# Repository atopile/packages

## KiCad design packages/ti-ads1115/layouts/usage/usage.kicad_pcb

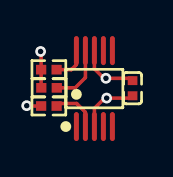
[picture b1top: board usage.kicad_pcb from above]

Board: 2 copper layers, 5 parts (0 on the bottom side), 6 nets.

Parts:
C1: 100nF; C0402
R1, R2, R3: 10kΩ; R0402
U1: MSOP-10_L3.0-W3.0-P0.50-LS5.0-BL

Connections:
ALERT_RDY: R1.1, U1.2
SCL: R2.1, U1.10
SDA: R3.1, U1.9
hv: C1.1, U1.8
i2c-hv: R2.2, R3.2
lv: C1.2, U1.1, U1.3

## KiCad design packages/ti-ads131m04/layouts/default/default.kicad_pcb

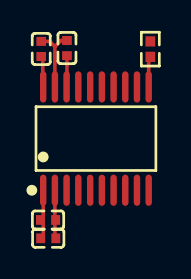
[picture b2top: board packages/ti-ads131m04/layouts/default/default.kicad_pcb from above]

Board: 2 copper layers, 6 parts (0 on the bottom side), 5 nets.

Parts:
C1, C3: 0.000001F; C0402
C2, C4: 0.0000001F; C0402
R1: 10000Ω; R0402
U1: TSSOP-20_L6.5-W4.4-P0.65-LS6.4-BL

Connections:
cap_bypass-power-hv: C3.1, U1.18
dvdd_decap-power-hv: C4.1, R1.2, U1.20
hv: C1.1, C2.1, U1.1
lv: C1.2, C2.2, C3.2, C4.2, U1.2, U1.19
nSYNC_nRESET: R1.1, U1.11

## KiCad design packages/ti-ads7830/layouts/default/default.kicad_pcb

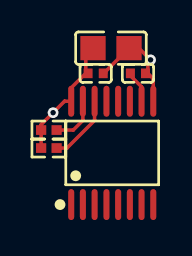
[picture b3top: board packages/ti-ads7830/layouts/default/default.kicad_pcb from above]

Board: 2 copper layers, 6 parts (0 on the bottom side), 5 nets.

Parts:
C1, C2: 1±10.0%F; C0402
C3: {8.999..1.1}F; C0805
R1, R2: 10000±1.0%Ω; R0402
U1: TSSOP-16_L5.0-W4.4-P0.65-LS6.4-BL

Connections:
SCL: R1.1, U1.14
SDA: R2.1, U1.15
decoup_ref-power-hv: C2.1, U1.10
hv: C1.1, C3.1, R1.2, R2.2, U1.16
lv: C1.2, C2.2, C3.2, U1.9, U1.12, U1.13

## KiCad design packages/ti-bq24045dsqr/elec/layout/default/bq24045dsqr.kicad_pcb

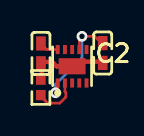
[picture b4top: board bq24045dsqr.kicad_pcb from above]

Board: 2 copper layers, 4 parts (0 on the bottom side), 4 nets.

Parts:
C1, C2: 1µF ±10% 25V X5R; C0402-b3ef17
R1: 560Ω ±1% 62.5mW; R0402-56259e
U1: WSON-10_L2.0-W2.0-P0.40-BL-EP

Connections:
IN: C1.1, U1.1, U1.7
ISET: R1.1, U1.2
OUT: C2.1, U1.10
gnd: C1.2, C2.2, R1.2, U1.3, U1.11
